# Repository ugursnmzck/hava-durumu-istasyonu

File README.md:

# Hava Durumu İstasyonu

V2.0 Yapılan Değişiklikler:
- CAD yazılımı olarak Autodesk Eagle bırakılarak KiCAD kullanıldı.
- Mikroişlemci devresinde dijital güç girişlerinin tamamına filtre kondansatörü eklendi.
- Sıcaklık sensörünün çalışmasını engelleyen filtre kondansatörüne ait bağlantı hatası düzeltildi.
- PCB 4 katmanlı olarak yeniden tasarlandı.

V1.0:

Sıcaklık, nem ve basınç verileri sensörler yardımıyla okunarak kablosuz bir şekilde bilgisayara iletilmektedir.

Sıcaklık ve nem sensörü olarak SHT30, basınç sensörü olarak ise BMP280 kullanılmıştır. Mikrodenetleyici olarak STM32F103C8T6 tercih edilmiştir. Sensör verilerinin yanında pil geirlimi ve gerçek zamanlı saat verisi de mikrodenetleyici ile oluşturulmaktadır. Kablosuz haberleşme için ESP8266-01 modülü tercih edilmiştir. Gömülü sistem kodları C dilinde STM32 CubeIDE üzerinde yazılmıştır. Grafik arayüzü Visual Studio üzerinde C# dili ile hazırlanmıştır. Arayüz tasarımında .NET Framework ve SimpleTCP eklentisi gereklidir.

Gerekli PCB tasarımı Autodesk Eagle ile yapılmıştır.

Proje elektrik elektronik mühendisliği lisans bitirme projesi olarak tasarlanmıştır.

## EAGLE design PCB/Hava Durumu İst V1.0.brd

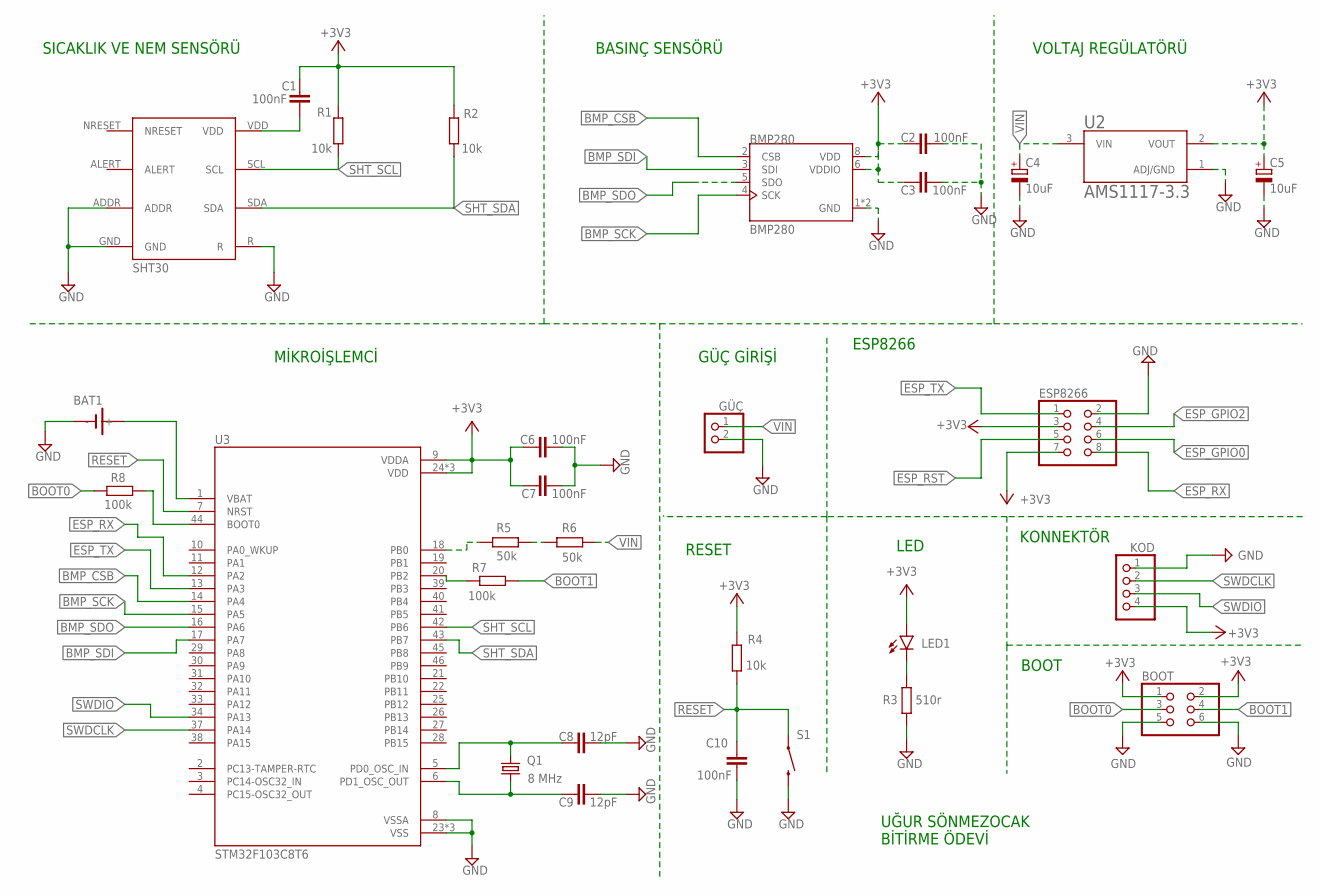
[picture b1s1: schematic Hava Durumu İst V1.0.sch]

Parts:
BAT1: SN2032
BMP280: BMP280; XDCR_BMP280
BOOT: PINHD-2X3; 2X03
C1, C2, C3, C6, C7, C10: 100nF; C0805
C4, C5: 10uF; SMC_P
C8, C9: 12pF; C0805
ESP8266: PINHD-2X4; 2X04
GÜÇ: PINHD-1X2; 1X02
KOD: PINHD-1X4/90; 1X04/90
LED1: LEDCHIP-LED0805; CHIP-LED0805
Q1: 8 MHz; HC49UP
R1, R2, R4: 10k; R0805
R3: 510r; R0805
R5, R6: 50k; R0805
R7, R8: 100k; R0805
S1: MOMENTARY-SWITCH-SPST-PTH-6.0MM; TACTILE_SWITCH_PTH_6.0MM
U2: AMS1117-3.3; SOT229P700X180-4N
U3: STM32F103C8T6; QFP50P900X900X160-48N
U$1: SHT30; SON50P250X250X90-9T100X170N

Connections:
+3V3: BMP280.6 (VDDIO), BMP280.8 (VDD), BOOT.1, BOOT.2, C1.1, C2.1, C3.1, C5.+, C6.1, C7.1, ESP8266.3, ESP8266.7, KOD.4, LED1.A, R1.2, R2.2, R4.2, U2.2 (VOUT), U3.9 (VDDA), U3.24 (VDD), U3.36 (VDD), U3.48 (VDD)
BMP_CSB: BMP280.2 (CSB), U3.14 (PA4)
BMP_SCK: BMP280.4 (SCK), U3.15 (PA5)
BMP_SDI: BMP280.3 (SDI), U3.17 (PA7)
BMP_SDO: BMP280.5 (SDO), U3.16 (PA6)
BOOT0: BOOT.3, R8.2
BOOT1: BOOT.4, R7.1
ESP_GPIO0: ESP8266.6
ESP_GPIO2: ESP8266.4
ESP_RST: ESP8266.5
ESP_RX: ESP8266.8, U3.12 (PA2)
ESP_TX: ESP8266.1, U3.13 (PA3)
GND: BAT1.-, BMP280.1 (GND), BMP280.7 (GND), BOOT.5, BOOT.6, C2.2, C3.2, C4.-, C5.-, C6.2, C7.2, C8.2, C9.2, C10.1, ESP8266.2, GÜÇ.2, KOD.1, R3.1, S1.3 (2), U2.1 (ADJ/GND), U3.8 (VSSA), U3.23 (VSS), U3.35 (VSS), U3.47 (VSS), U$1.ADDR, U$1.GND, U$1.R
unnamed: C1.2, U$1.VDD
unnamed: C9.1, Q1.1, U3.6 (PD1_OSC_OUT)
unnamed: C8.1, Q1.2, U3.5 (PD0_OSC_IN)
unnamed: R5.2, U3.18 (PB0)
unnamed: R5.1, R6.2
unnamed: LED1.C, R3.2
unnamed: BAT1.+, U3.1 (VBAT)
unnamed: R8.1, U3.44 (BOOT0)
unnamed: R7.2, U3.20 (PB2)
RESET: C10.2, R4.1, S1.1, U3.7 (NRST)
SHT_SCL: R1.1, U3.42 (PB6), U$1.SCL
SHT_SDA: R2.1, U3.43 (PB7), U$1.SDA
SWDCLK: KOD.2, U3.37 (PA14)
SWDIO: KOD.3, U3.34 (PA13)
VIN: C4.+, GÜÇ.1, R6.1, U2.3 (VIN)

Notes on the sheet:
SICAKLIK VE NEM SENSÖRÜ
BASINÇ SENSÖRÜ
VOLTAJ REGÜLATÖRÜ
ESP8266
LED
KONNEKTÖR
BOOT
RESET
GÜÇ GİRİŞİ
MİKROİŞLEMCİ
UĞUR SÖNMEZOCAK BİTİRME ÖDEVİ

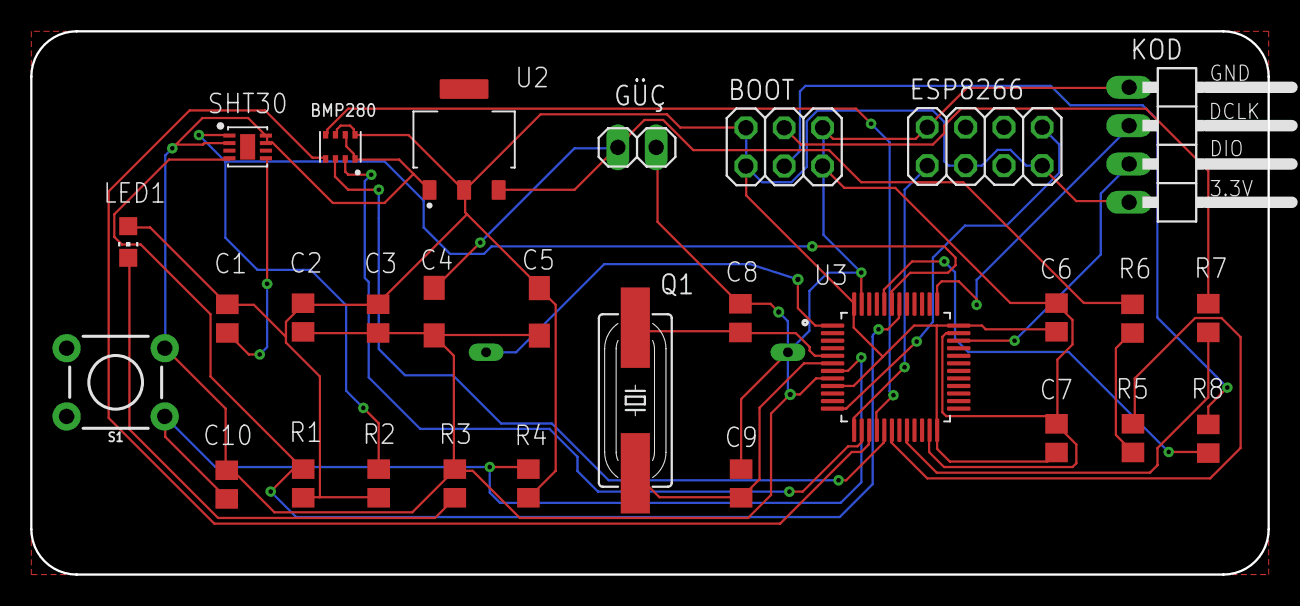
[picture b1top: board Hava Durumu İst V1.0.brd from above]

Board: 2 copper layers, 82.0 x 36.0 mm, 30 parts (1 on the bottom side), 25 nets.

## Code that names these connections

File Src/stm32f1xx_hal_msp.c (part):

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
    __HAL_RCC_GPIOB_CLK_ENABLE();
    /**ADC1 GPIO Configuration
    PB0     ------> ADC1_IN8
    */
    GPIO_InitStruct.Pin = GPIO_PIN_0;
    GPIO_InitStruct.Mode = GPIO_MODE_ANALOG;
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    __HAL_RCC_ADC1_CLK_DISABLE();

    /**ADC1 GPIO Configuration
    PB0     ------> ADC1_IN8
    */
    HAL_GPIO_DeInit(GPIOB, GPIO_PIN_0);

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
    __HAL_RCC_GPIOB_CLK_ENABLE();
    /**I2C1 GPIO Configuration
    PB6     ------> I2C1_SCL
    PB7     ------> I2C1_SDA
    */
    GPIO_InitStruct.Pin = GPIO_PIN_6|GPIO_PIN_7;
    GPIO_InitStruct.Mode = GPIO_MODE_AF_OD;
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    __HAL_RCC_I2C1_CLK_DISABLE();

    /**I2C1 GPIO Configuration
    PB6     ------> I2C1_SCL
    PB7     ------> I2C1_SDA
    */
    HAL_GPIO_DeInit(GPIOB, GPIO_PIN_6);

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
    __HAL_RCC_GPIOA_CLK_ENABLE();
    /**SPI1 GPIO Configuration
    PA4     ------> SPI1_NSS
    PA5     ------> SPI1_SCK
    PA6     ------> SPI1_MISO
    PA7     ------> SPI1_MOSI
    */
    GPIO_InitStruct.Pin = GPIO_PIN_4|GPIO_PIN_5|GPIO_PIN_7;
    GPIO_InitStruct.Mode = GPIO_MODE_AF_PP;
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    __HAL_RCC_SPI1_CLK_DISABLE();

    /**SPI1 GPIO Configuration
    PA4     ------> SPI1_NSS
    PA5     ------> SPI1_SCK
    PA6     ------> SPI1_MISO
    PA7     ------> SPI1_MOSI
    */
    HAL_GPIO_DeInit(GPIOA, GPIO_PIN_4|GPIO_PIN_5|GPIO_PIN_6|GPIO_PIN_7);

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
    __HAL_RCC_GPIOA_CLK_ENABLE();
    /**USART2 GPIO Configuration
    PA2     ------> USART2_TX
    PA3     ------> USART2_RX
    */
    GPIO_InitStruct.Pin = GPIO_PIN_2;
    GPIO_InitStruct.Mode = GPIO_MODE_AF_PP;
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    __HAL_RCC_USART2_CLK_DISABLE();

    /**USART2 GPIO Configuration
    PA2     ------> USART2_TX
    PA3     ------> USART2_RX
    */
    HAL_GPIO_DeInit(GPIOA, GPIO_PIN_2|GPIO_PIN_3);

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
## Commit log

2021-11-04 Create asd

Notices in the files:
Src/stm32f1xx_hal_msp.c:
© Copyright (c) 2021 STMicroelectronics.
All rights reserved.
This software component is licensed by ST under BSD 3-Clause license,
the "License"; You may not use this file except in compliance with the
License. You may obtain a copy of the License at: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
(C) COPYRIGHT STMicroelectronics *****END OF FILE
parts and their libraries:
SparkFun-Switches: Licensing: Creative Commons ShareAlike 4.0 International - https://creativecommons.org/licenses/by-sa/4.0
